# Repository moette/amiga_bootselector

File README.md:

# amiga_bootselector
ATMega based Amiga Bootselector

This is an ALPHA Version. It will NOT work out of the BOX!

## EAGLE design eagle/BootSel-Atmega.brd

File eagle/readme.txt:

This bootselector is using an ATMega-8 controller to realize a "smart" bootselector.

The work is (c) Marko Oette. It is licensed under the GPL v. 3. See LICENSE file.

Ths is a work in progress!

-- Marko Oette
http://www.oette.info
http://retro.oette.info
marko@oette.info

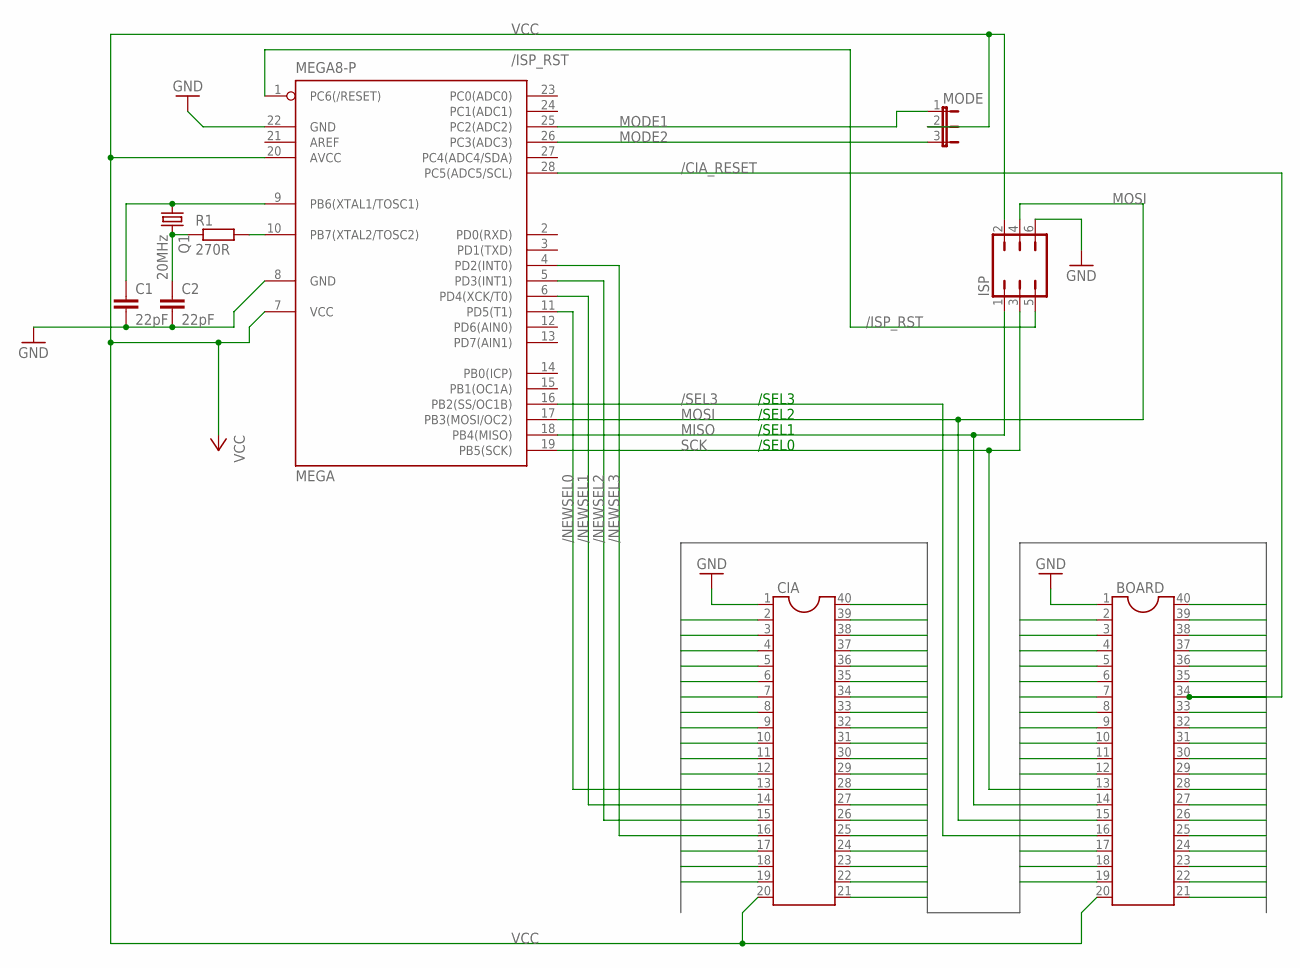
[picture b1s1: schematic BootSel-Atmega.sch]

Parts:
BOARD: DIL40
C1, C2: 22pF; C2.5-4
CIA: DIL40
ISP: JP3Q
MEGA: MEGA8-P; DIL28-3
MODE: JP2E; JP2
Q1: 20MHz; HC49/S
R1: 270R; 0204/5

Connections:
/CIA_RESET: BOARD.34, CIA.34, MEGA.28 (PC5(ADC5/SCL))
/ISP_RST: ISP.5, MEGA.1 (PC6(/RESET))
/NEWSEL0: CIA.13, MEGA.11 (PD5(T1))
/NEWSEL1: CIA.14, MEGA.6 (PD4(XCK/T0))
/NEWSEL2: CIA.15, MEGA.5 (PD3(INT1))
/NEWSEL3: CIA.16, MEGA.4 (PD2(INT0))
/SEL3: BOARD.16, MEGA.16 (PB2(SS/OC1B))
CIA2: BOARD.2, CIA.2
CIA3: BOARD.3, CIA.3
CIA4: BOARD.4, CIA.4
CIA5: BOARD.5, CIA.5
CIA6: BOARD.6, CIA.6
CIA7: BOARD.7, CIA.7
CIA8: BOARD.8, CIA.8
CIA9: BOARD.9, CIA.9
CIA10: BOARD.10, CIA.10
CIA11: BOARD.11, CIA.11
CIA12: BOARD.12, CIA.12
CIA17: BOARD.17, CIA.17
CIA18: BOARD.18, CIA.18
CIA19: BOARD.19, CIA.19
CIA21: BOARD.21, CIA.21
CIA22: BOARD.22, CIA.22
CIA23: BOARD.23, CIA.23
CIA24: BOARD.24, CIA.24
CIA25: BOARD.25, CIA.25
CIA26: BOARD.26, CIA.26
CIA27: BOARD.27, CIA.27
CIA28: BOARD.28, CIA.28
CIA29: BOARD.29, CIA.29
CIA30: BOARD.30, CIA.30
CIA31: BOARD.31, CIA.31
CIA32: BOARD.32, CIA.32
CIA33: BOARD.33, CIA.33
CIA35: BOARD.35, CIA.35
CIA36: BOARD.36, CIA.36
CIA37: BOARD.37, CIA.37
CIA38: BOARD.38, CIA.38
CIA39: BOARD.39, CIA.39
CIA40: BOARD.40, CIA.40
GND: BOARD.1, C1.2, C2.2, CIA.1, ISP.6, MEGA.8 (GND), MEGA.22 (GND)
MISO: BOARD.14, ISP.1, MEGA.18 (PB4(MISO))
MODE1: MEGA.25 (PC2(ADC2)), MODE.1
MODE2: MEGA.26 (PC3(ADC3)), MODE.3
MOSI: BOARD.15, ISP.4, MEGA.17 (PB3(MOSI/OC2))
unnamed: MEGA.10 (PB7(XTAL2/TOSC2)), R1.2
unnamed: C2.1, Q1.2, R1.1
unnamed: C1.1, MEGA.9 (PB6(XTAL1/TOSC1)), Q1.1
SCK: BOARD.13, ISP.3, MEGA.19 (PB5(SCK))
VCC: BOARD.20, CIA.20, ISP.2, MEGA.7 (VCC), MEGA.20 (AVCC), MODE.2

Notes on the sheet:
/SEL0
/SEL1
/SEL2
/SEL3

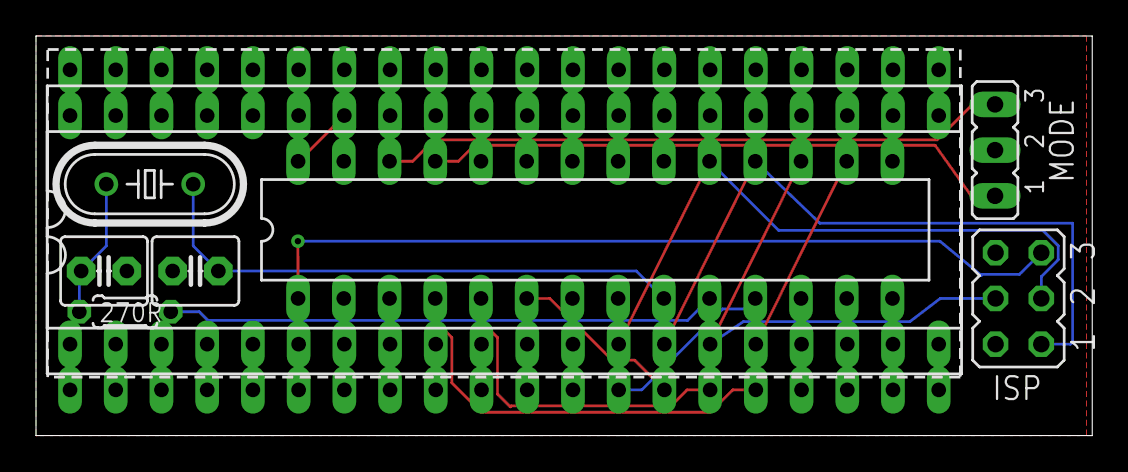
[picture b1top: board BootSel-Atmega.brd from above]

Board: 2 copper layers, 58.7 x 22.2 mm, 9 parts (0 on the bottom side), 50 nets.

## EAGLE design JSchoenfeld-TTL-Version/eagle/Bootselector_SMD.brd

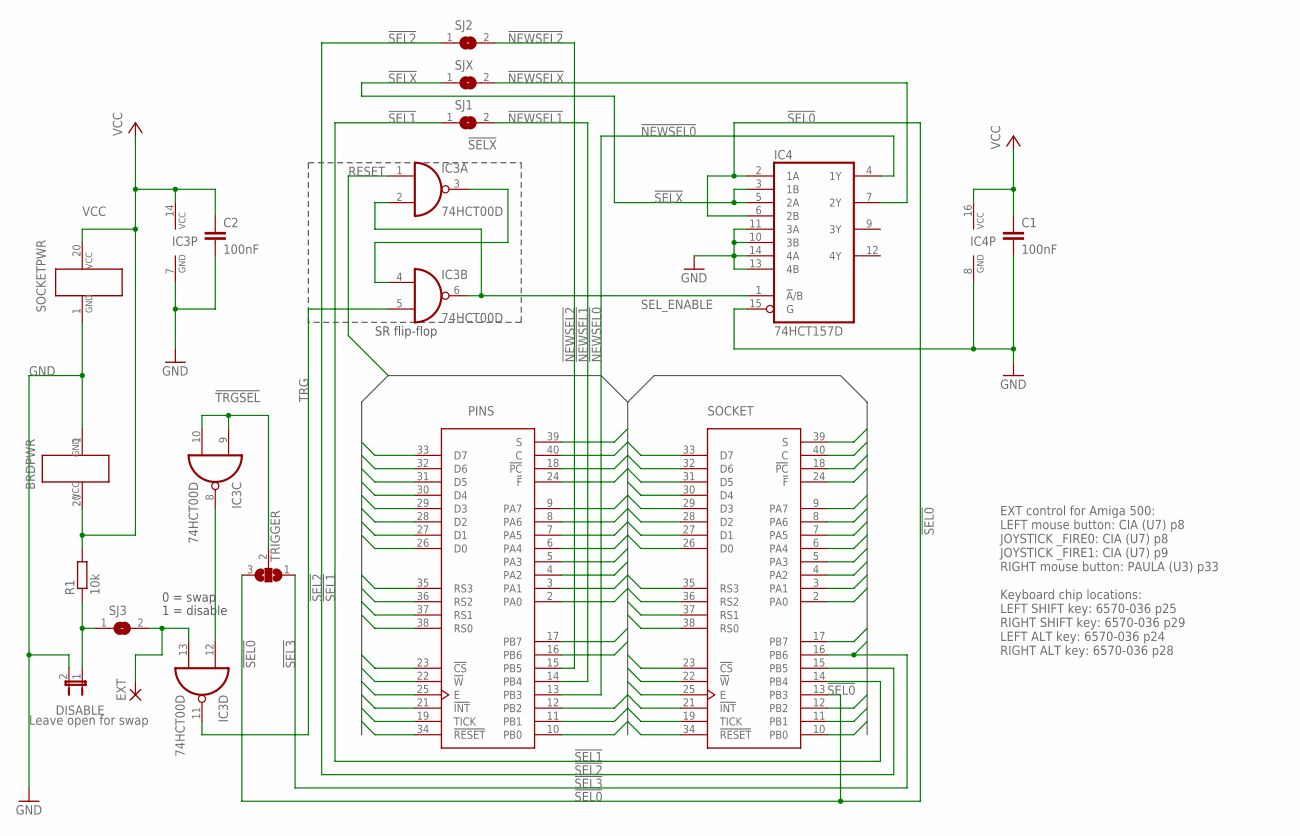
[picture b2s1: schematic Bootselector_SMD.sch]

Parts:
BRD: PINS; DIP40-6
C1: 100nF; C0805
C2: 100nF; C0805K
DISABLE: Leave open for swap; JP1
EXT: SMD2; SMD1,27-2,54
IC3: 74HCT00D; SO14
IC4: 74HCT157D; SO16
R1: 10k; R0805
SJ1, SJ2, SJ3: SJ
SJX: SJ
SOCKET: CIA_DIP; DIP40-6
TRIGGER: SJ2W; SJ_2

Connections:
!NEWSEL0: BRD.13 (PB3), IC4.4 (1Y)
!NEWSEL1: BRD.14 (PB4), SJ1.2
!NEWSEL2: BRD.15 (PB5), SJ2.2
!NEWSELX: IC4.7 (2Y), SJX.2
!SEL0: IC4.2 (1A), IC4.6 (2B), SOCKET.13 (PB3), TRIGGER.3
!SEL1: SJ1.1, SOCKET.14 (PB4)
!SEL2: SJ2.1, SOCKET.15 (PB5)
!SEL3: BRD.16 (PB6), SOCKET.16 (PB6), TRIGGER.1
!SELX: IC4.3 (1B), IC4.5 (2A), SJX.1
!TRGSEL: IC3.9 (I0), IC3.10 (I1), TRIGGER.2
C: BRD.40 (C), SOCKET.40 (C)
CS: BRD.23 (!CS), SOCKET.23 (!CS)
D0: BRD.26 (D0), SOCKET.26 (D0)
D1: BRD.27 (D1), SOCKET.27 (D1)
D2: BRD.28 (D2), SOCKET.28 (D2)
D3: BRD.29 (D3), SOCKET.29 (D3)
D4: BRD.30 (D4), SOCKET.30 (D4)
D5: BRD.31 (D5), SOCKET.31 (D5)
D6: BRD.32 (D6), SOCKET.32 (D6)
D7: BRD.33 (D7), SOCKET.33 (D7)
E: BRD.25 (E), SOCKET.25 (E)
F: BRD.24 (!F), SOCKET.24 (!F)
GND: BRD.1 (GND1), C1.2, C2.2, DISABLE.2, IC3.7 (GND), IC4.8 (GND), IC4.10 (3B), IC4.11 (3A), IC4.13 (4B), IC4.14 (4A), IC4.15 (G), SOCKET.1 (GND1)
INT: BRD.21 (!INT), SOCKET.21 (!INT)
unnamed: EXT.1, IC3.13 (I1), SJ3.2
unnamed: IC3.8 (O), IC3.12 (I0)
unnamed: IC3.3 (O), IC3.4 (I0)
unnamed: DISABLE.1, R1.1, SJ3.1
PA0: BRD.2 (PA0), SOCKET.2 (PA0)
PA1: BRD.3 (PA1), SOCKET.3 (PA1)
PA2: BRD.4 (PA2), SOCKET.4 (PA2)
PA3: BRD.5 (PA3), SOCKET.5 (PA3)
PA4: BRD.6 (PA4), SOCKET.6 (PA4)
PA5: BRD.7 (PA5), SOCKET.7 (PA5)
PA6: BRD.8 (PA6), SOCKET.8 (PA6)
PA7: BRD.9 (PA7), SOCKET.9 (PA7)
PB0: BRD.10 (PB0), SOCKET.10 (PB0)
PB1: BRD.11 (PB1), SOCKET.11 (PB1)
PB2: BRD.12 (PB2), SOCKET.12 (PB2)
PB7: BRD.17 (PB7), SOCKET.17 (PB7)
PC: BRD.18 (!PC), SOCKET.18 (!PC)
RESET: BRD.34 (!RESET), IC3.1 (I0), SOCKET.34 (!RESET)
RS0: BRD.38 (RS0), SOCKET.38 (RS0)
RS1: BRD.37 (RS1), SOCKET.37 (RS1)
RS2: BRD.36 (RS2), SOCKET.36 (RS2)
RS3: BRD.35 (RS3), SOCKET.35 (RS3)
S: BRD.39 (S), SOCKET.39 (S)
SEL_ENABLE: IC3.2 (I1), IC3.6 (O), IC4.1 (!A!/B)
TICK: BRD.19 (TICK), SOCKET.19 (TICK)
TRG: IC3.5 (I1), IC3.11 (O)
VCC: BRD.20 (VCC1), C1.1, C2.1, IC3.14 (VCC), IC4.16 (VCC), R1.2, SOCKET.20 (VCC1)
W: BRD.22 (!W), SOCKET.22 (!W)

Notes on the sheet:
SR flip-flop
1 = disable
0 = swap
EXT control for Amiga 500: LEFT mouse button: CIA (U7) p8 JOYSTICK _FIRE0: CIA (U7) p8 JOYSTICK _FIRE1: CIA (U7) p9 RIGHT mouse button: PAULA (U3) p33 Keyboard chip locations: LEFT SHIFT key: 6570-036 p25 RIGHT SHIFT key: 6570-036 p29 LEFT ALT key: 6570-036 p24 RIGHT ALT key: 6570-036 p28

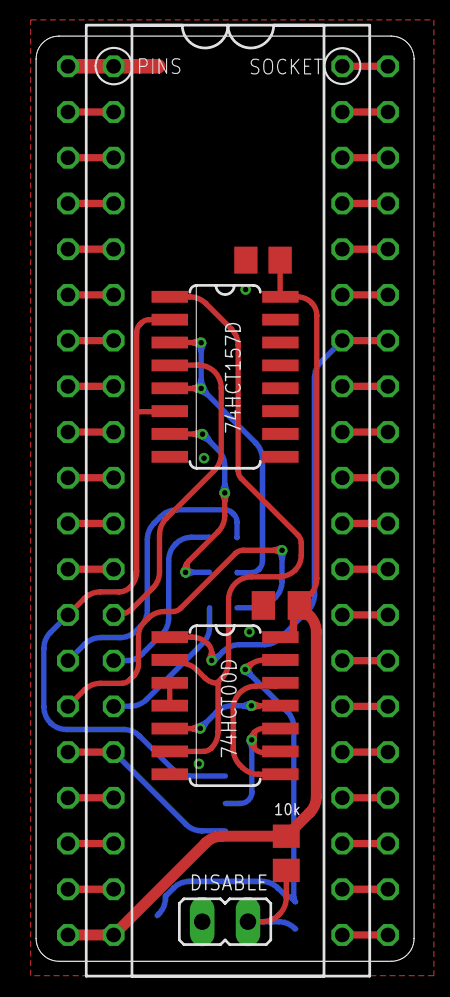
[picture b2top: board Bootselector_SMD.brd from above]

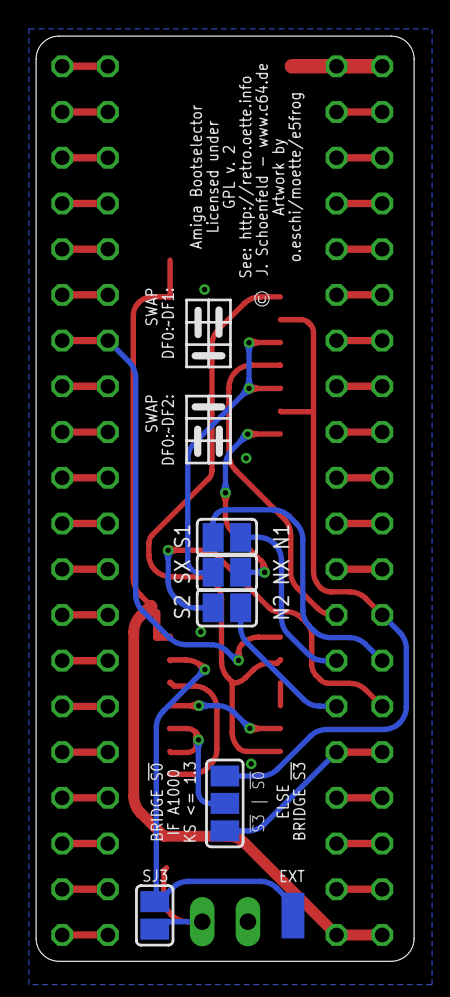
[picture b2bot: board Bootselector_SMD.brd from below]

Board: 2 copper layers, 21.0 x 51.4 mm, 14 parts (6 on the bottom side), 52 nets.

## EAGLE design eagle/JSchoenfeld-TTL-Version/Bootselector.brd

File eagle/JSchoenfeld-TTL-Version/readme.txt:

This bootselector is based on the idea of Jens Schönfeld (www.c64.de) to create a bootselector by only using TTL chips.
Jens licensed the schemantics under the GPL version 2. See LICENSE file!

Oliver Eschenbach created a first Eagle layout based upon that schemanctics and handed them over to me (Marko Oette).

I took over to add several other functions to the boot selector. Eg. make it useable on the A2000 / A3000.

For the general discussion see http://www.a1k.org/forum/showthread.php?t=23154

-- Marko Oette
http://www.oette.info
http://retro.oette.info
marko@oette.info

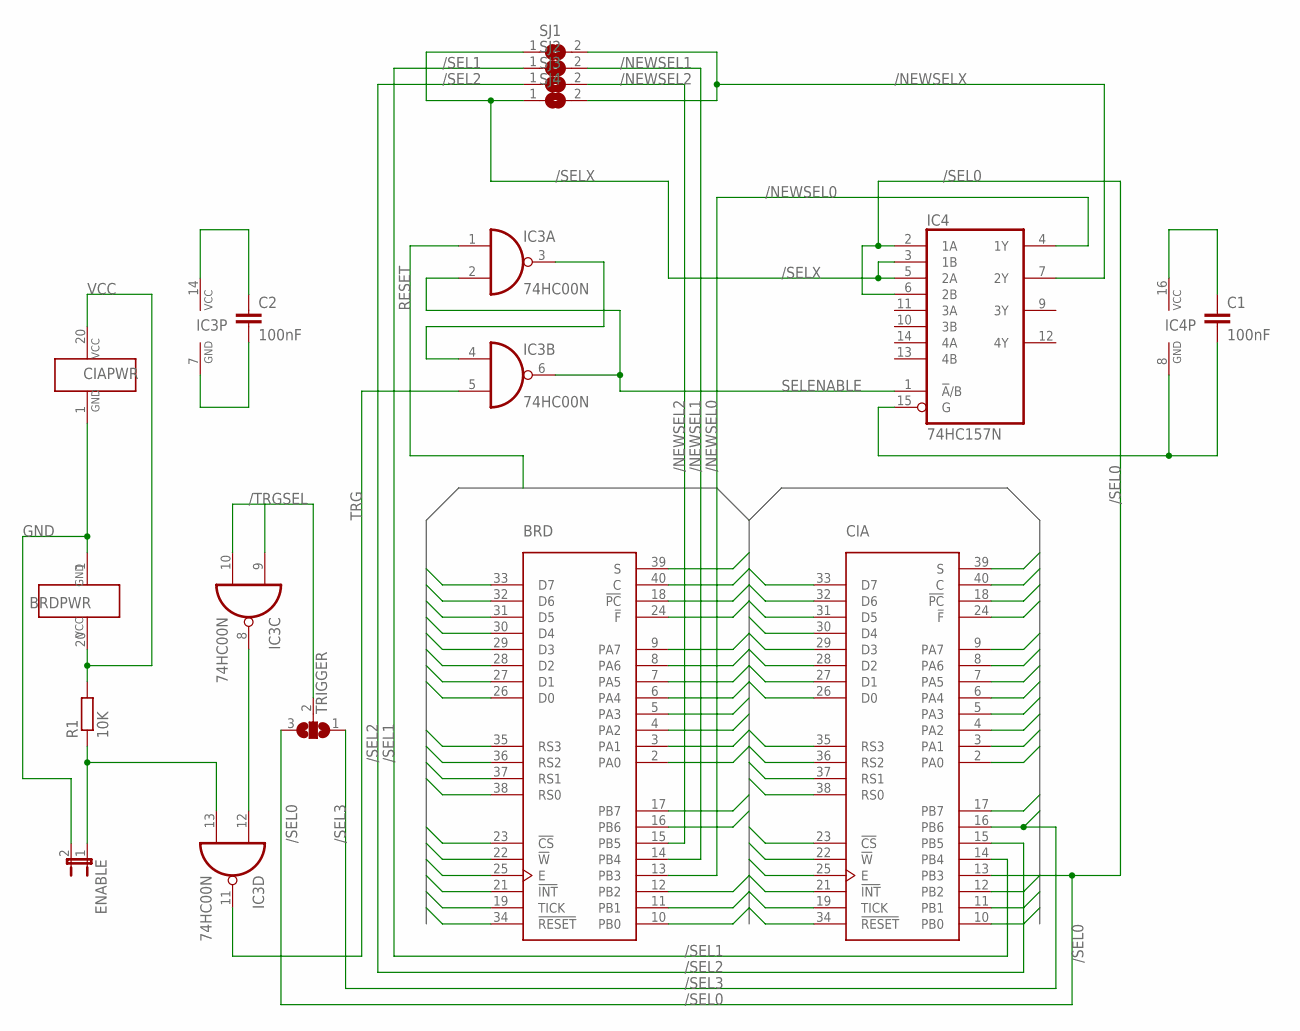
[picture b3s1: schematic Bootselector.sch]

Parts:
BRD: CIA_DIP; DIP40-6
C1, C2: 100nF; C050-025X075
CIA: CIA_DIP; DIP40-6
ENABLE: JP1E; JP1
IC3: 74HC00N; DIL14
IC4: 74HC157N; DIL16
R1: 10K; 0207/10
SJ1, SJ2, SJ3, SJ4: SJ
TRIGGER: SJ2W; SJ_2

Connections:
/NEWSEL0: BRD.13 (PB3), IC4.4 (1Y)
/NEWSEL1: BRD.14 (PB4), SJ2.2
/NEWSEL2: BRD.15 (PB5), SJ3.2
/NEWSELX: IC4.7 (2Y), SJ1.2, SJ4.2
/SEL0: CIA.13 (PB3), IC4.2 (1A), IC4.6 (2B), TRIGGER.3
/SEL1: CIA.14 (PB4), SJ2.1
/SEL2: CIA.15 (PB5), SJ3.1
/SEL3: BRD.16 (PB6), CIA.16 (PB6), TRIGGER.1
/SELX: IC4.3 (1B), IC4.5 (2A), SJ1.1, SJ4.1
/TRGSEL: IC3.9 (I0), IC3.10 (I1), TRIGGER.2
C: BRD.40 (C), CIA.40 (C)
CS: BRD.23 (!CS), CIA.23 (!CS)
D0: BRD.26 (D0), CIA.26 (D0)
D1: BRD.27 (D1), CIA.27 (D1)
D2: BRD.28 (D2), CIA.28 (D2)
D3: BRD.29 (D3), CIA.29 (D3)
D4: BRD.30 (D4), CIA.30 (D4)
D5: BRD.31 (D5), CIA.31 (D5)
D6: BRD.32 (D6), CIA.32 (D6)
D7: BRD.33 (D7), CIA.33 (D7)
E: BRD.25 (E), CIA.25 (E)
F: BRD.24 (!F), CIA.24 (!F)
GND: BRD.1 (GND1), C1.2, C2.2, CIA.1 (GND1), ENABLE.2, IC3.7 (GND), IC4.8 (GND), IC4.15 (G)
INT: BRD.21 (!INT), CIA.21 (!INT)
unnamed: ENABLE.1, IC3.13 (I1), R1.1
unnamed: IC3.8 (O), IC3.12 (I0)
unnamed: IC3.3 (O), IC3.4 (I0)
PA0: BRD.2 (PA0), CIA.2 (PA0)
PA1: BRD.3 (PA1), CIA.3 (PA1)
PA2: BRD.4 (PA2), CIA.4 (PA2)
PA3: BRD.5 (PA3), CIA.5 (PA3)
PA4: BRD.6 (PA4), CIA.6 (PA4)
PA5: BRD.7 (PA5), CIA.7 (PA5)
PA6: BRD.8 (PA6), CIA.8 (PA6)
PA7: BRD.9 (PA7), CIA.9 (PA7)
PB0: BRD.10 (PB0), CIA.10 (PB0)
PB1: BRD.11 (PB1), CIA.11 (PB1)
PB2: BRD.12 (PB2), CIA.12 (PB2)
PB7: BRD.17 (PB7), CIA.17 (PB7)
PC: BRD.18 (!PC), CIA.18 (!PC)
RESET: BRD.34 (!RESET), CIA.34 (!RESET), IC3.1 (I0)
RS0: BRD.38 (RS0), CIA.38 (RS0)
RS1: BRD.37 (RS1), CIA.37 (RS1)
RS2: BRD.36 (RS2), CIA.36 (RS2)
RS3: BRD.35 (RS3), CIA.35 (RS3)
S: BRD.39 (S), CIA.39 (S)
SELENABLE: IC3.2 (I1), IC3.6 (O), IC4.1 (!A!/B)
TICK: BRD.19 (TICK), CIA.19 (TICK)
TRG: IC3.5 (I1), IC3.11 (O)
VCC: BRD.20 (VCC1), C1.1, C2.1, CIA.20 (VCC1), IC3.14 (VCC), IC4.16 (VCC), R1.2
W: BRD.22 (!W), CIA.22 (!W)

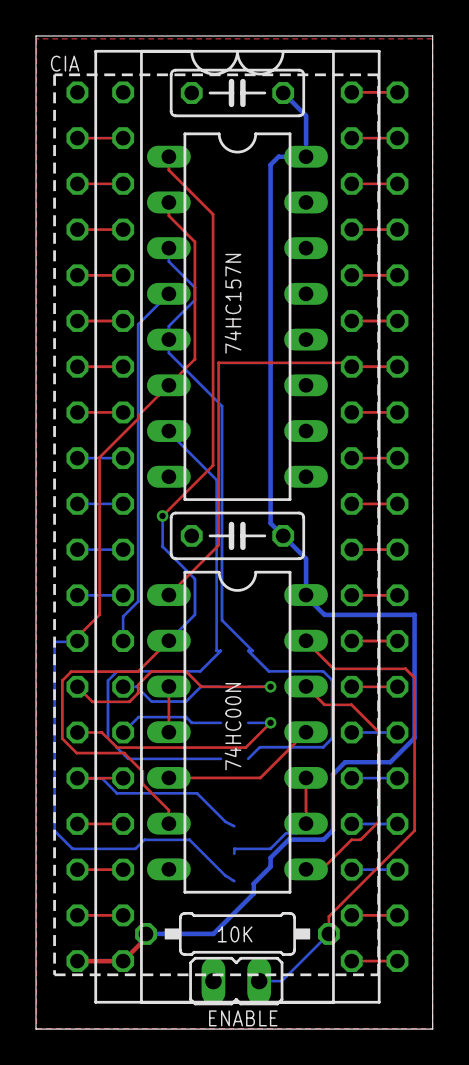
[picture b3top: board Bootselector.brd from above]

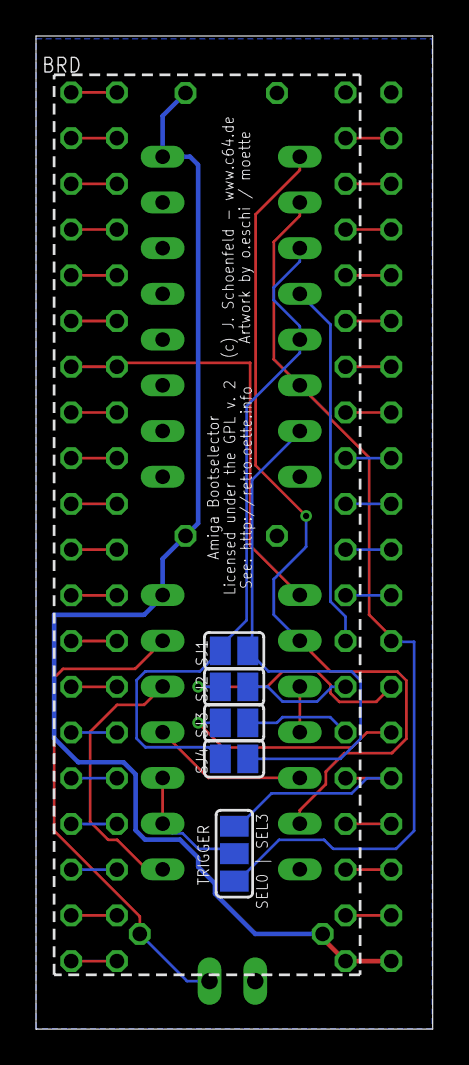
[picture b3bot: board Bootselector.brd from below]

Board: 2 copper layers, 22.0 x 55.2 mm, 13 parts (5 on the bottom side), 51 nets.

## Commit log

2017-12-10 Initial commit.
2017-12-16 timing fixes
2018-01-03 Adding Eagle files
2018-01-03 adding docs
2018-01-03 0.96
2018-01-07 smaller changes
2018-01-27 Added documentation.pdf for TTL version. Move TTL version one directory level up so it is easier to find.
2018-01-27 Documentation corrected.
2018-02-01 Changes by 'e5frog' - SMT version, updated THT version.
2018-02-25 25.02.2018 - Fredric QJ Blåholtz (e5frog) + Marko Oette (marko@oette.info) v. 0.98 - Prototyping v 0.97 done, works - Updated SMD version to match THT version - Updated documentation for THT version 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
2018-02-25 Fixed ISP connecotor.
2018-03-15 Added Gerber file with silk screen ;)

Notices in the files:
JSchoenfeld-TTL-Version/eagle/Bootselector_SMD.brd:
GPL v. 2
eagle/BootSel-Atmega.brd:
(c) 2018 Marko Oette
eagle/JSchoenfeld-TTL-Version/Bootselector.brd:
Licensed under the GPL v. 2
